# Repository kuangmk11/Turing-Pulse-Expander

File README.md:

# Turing Pulse Expander — archive

> **This repository is an archive.** The finished work has moved out into its own
> repositories; what remains here is upstream material and the studies that were
> superseded along the way.

| Live work | |
|---|---|
| **[Doubleplus_Pulses](https://github.com/kuangmk11/Doubleplus_Pulses)** | **Pulses Plus** — the built and tested hardware. KiCad schematic, PCB, panel v4, BOM, gerbers, and the full design write-up. CC BY-NC-SA 4.0. |
| **[Doubleplus_Pulses_VCV](https://github.com/kuangmk11/Doubleplus_Pulses_VCV)** | The VCV Rack 2 port of the same module. GPL-3.0-or-later. |

Both were extracted with `git subtree split`, so their commit history came with
them. Their files remain in this repository's history too, up to the commit that
removed them — nothing was rewritten here.

---

## What Pulses Plus is

A performance-oriented gate router for the Music Thing Turing Machine: eight pulse
channels, each switchable to one of two merge buses or off, with each bus computing
the OR or the AND of whatever is routed to it, chosen live from the panel. It
generalises the stock Pulses expander's four hard-wired AND outputs into any subset
of the eight bits, OR'd or AND'd, by hand.

See [Doubleplus_Pulses](https://github.com/kuangmk11/Doubleplus_Pulses) for the
design and the write-up.

---

## What's left here

### Upstream: Rev 2 Turing Pulse Expander

This repository is a fork of
[TomWhitwell/Turing-Pulse-Expander](https://github.com/TomWhitwell/Turing-Pulse-Expander),
and keeps that link deliberately — it is the right home for Tom Whitwell's files.

- `Hardware/pulses_rev2.brd`, `Hardware/pulses_rev2.sch` — the original Eagle design
- `Collateral/` — his gerbers, panel artwork and schematic PDF

The Rev 2 expander is a slightly updated Turing Machine Pulse Expander with more
outputs — SMD, but still an easy build. Its BOM:

- 1 × 4081 Quad AND Gate, SO14 package
- 11 × 3 mm LEDs
- 11 × 1k resistors, 1206
- 11 × 2k resistors, 1206 (LED protection — change the value for high-intensity LEDs)
- 11 × [Thonkiconn](https://www.thonk.co.uk/shop/thonkiconn-3-5mm-jack-sockets-x50/) sockets
- 1 × 16-pin header 2×8 (e.g. Mouser 649-67997-216HLF)
- 1 × ribbon cable

### Dead ends and studies

- `Docs/build_*.py`, `kfp.py`, `ksym.py`, `panel_geom.py`, `patch_footprints.py` —
  the generator scripts that built the earlier `pulses_plus` board from source.
  The finished module took a different route: it carries a single, much smaller
  `tools/build_panel.py` that regenerates only panel artwork from the v1 panel.
- `Docs/panel/` — two early panel layout studies (`v1-two-column-grid.html`,
  `v2-zigzag.html`) and the notes comparing them. The zig-zag won and became the
  shipped panel.
- `Hardware/pulses_plus/` — the superseded full-size design that preceded the
  sub-miniature-toggle version. **Present on disk but never committed**; it is
  gitignored and always has been, so it does not exist in this repository's
  history and will not appear in a fresh clone.
- Assorted scratch material at the repository root (`Chat.txt`, `path30.svg`,
  panel artwork exports) — likewise gitignored, on disk only.

---

## Licence

**Tom Whitwell's Rev 2 expander** — `Hardware/pulses_rev2.brd`, `Hardware/pulses_rev2.sch`
and `Collateral/` — is his, inherited by forking
[TomWhitwell/Turing-Pulse-Expander](https://github.com/TomWhitwell/Turing-Pulse-Expander).
Nothing here grants rights over it. For context, the parent
[Turing Machine](https://github.com/TomWhitwell/TuringMachine) project's README states
[CC-BY-SA 3.0](https://creativecommons.org/licenses/by-sa/3.0/), but that is not
stated in the expander repository itself.

**The Pulses Plus studies** in `Docs/` are Missing Mile Modular's, under
[CC BY-NC-SA 4.0](https://creativecommons.org/licenses/by-nc-sa/4.0/) — the same
terms as the finished hardware.

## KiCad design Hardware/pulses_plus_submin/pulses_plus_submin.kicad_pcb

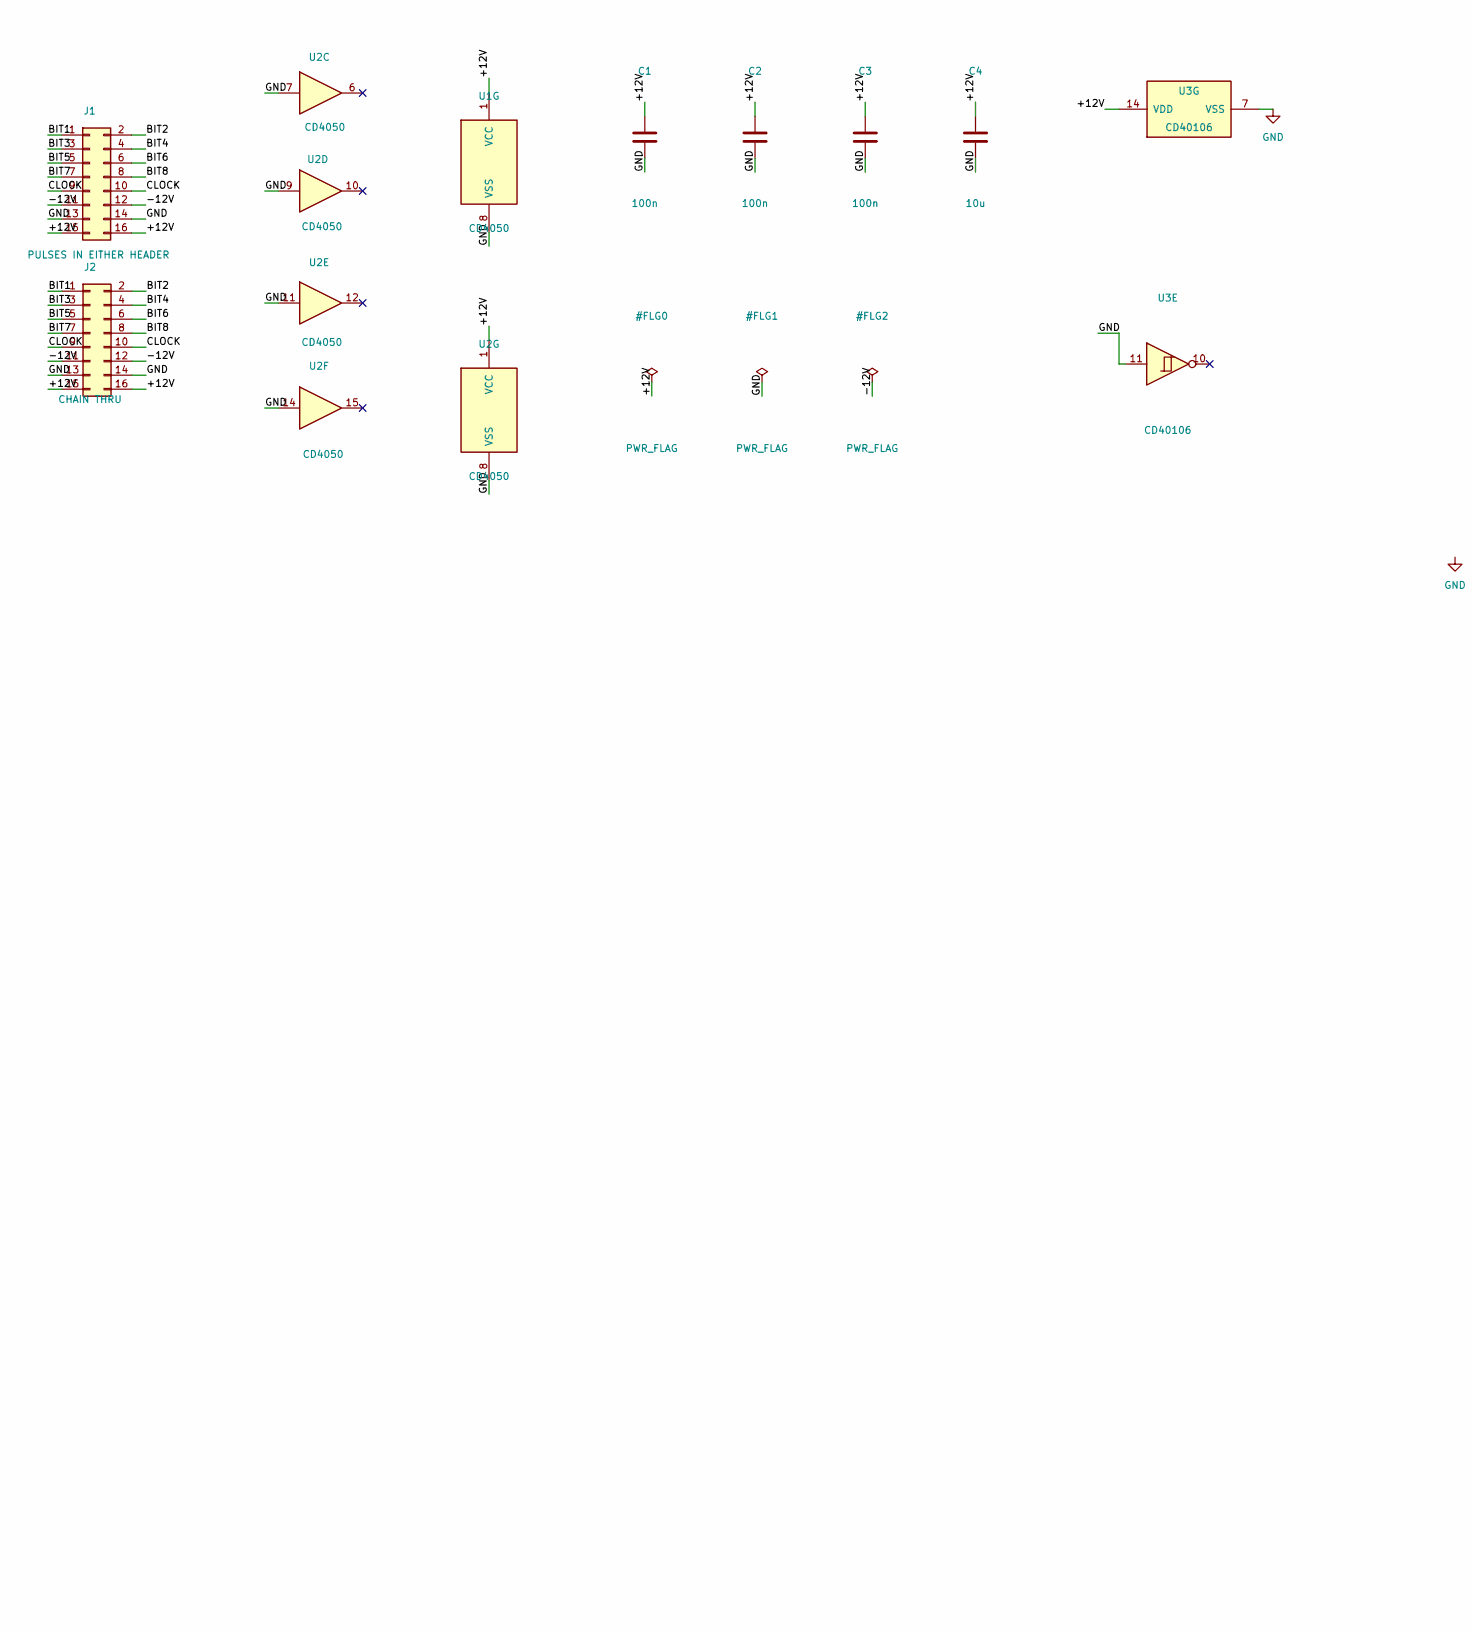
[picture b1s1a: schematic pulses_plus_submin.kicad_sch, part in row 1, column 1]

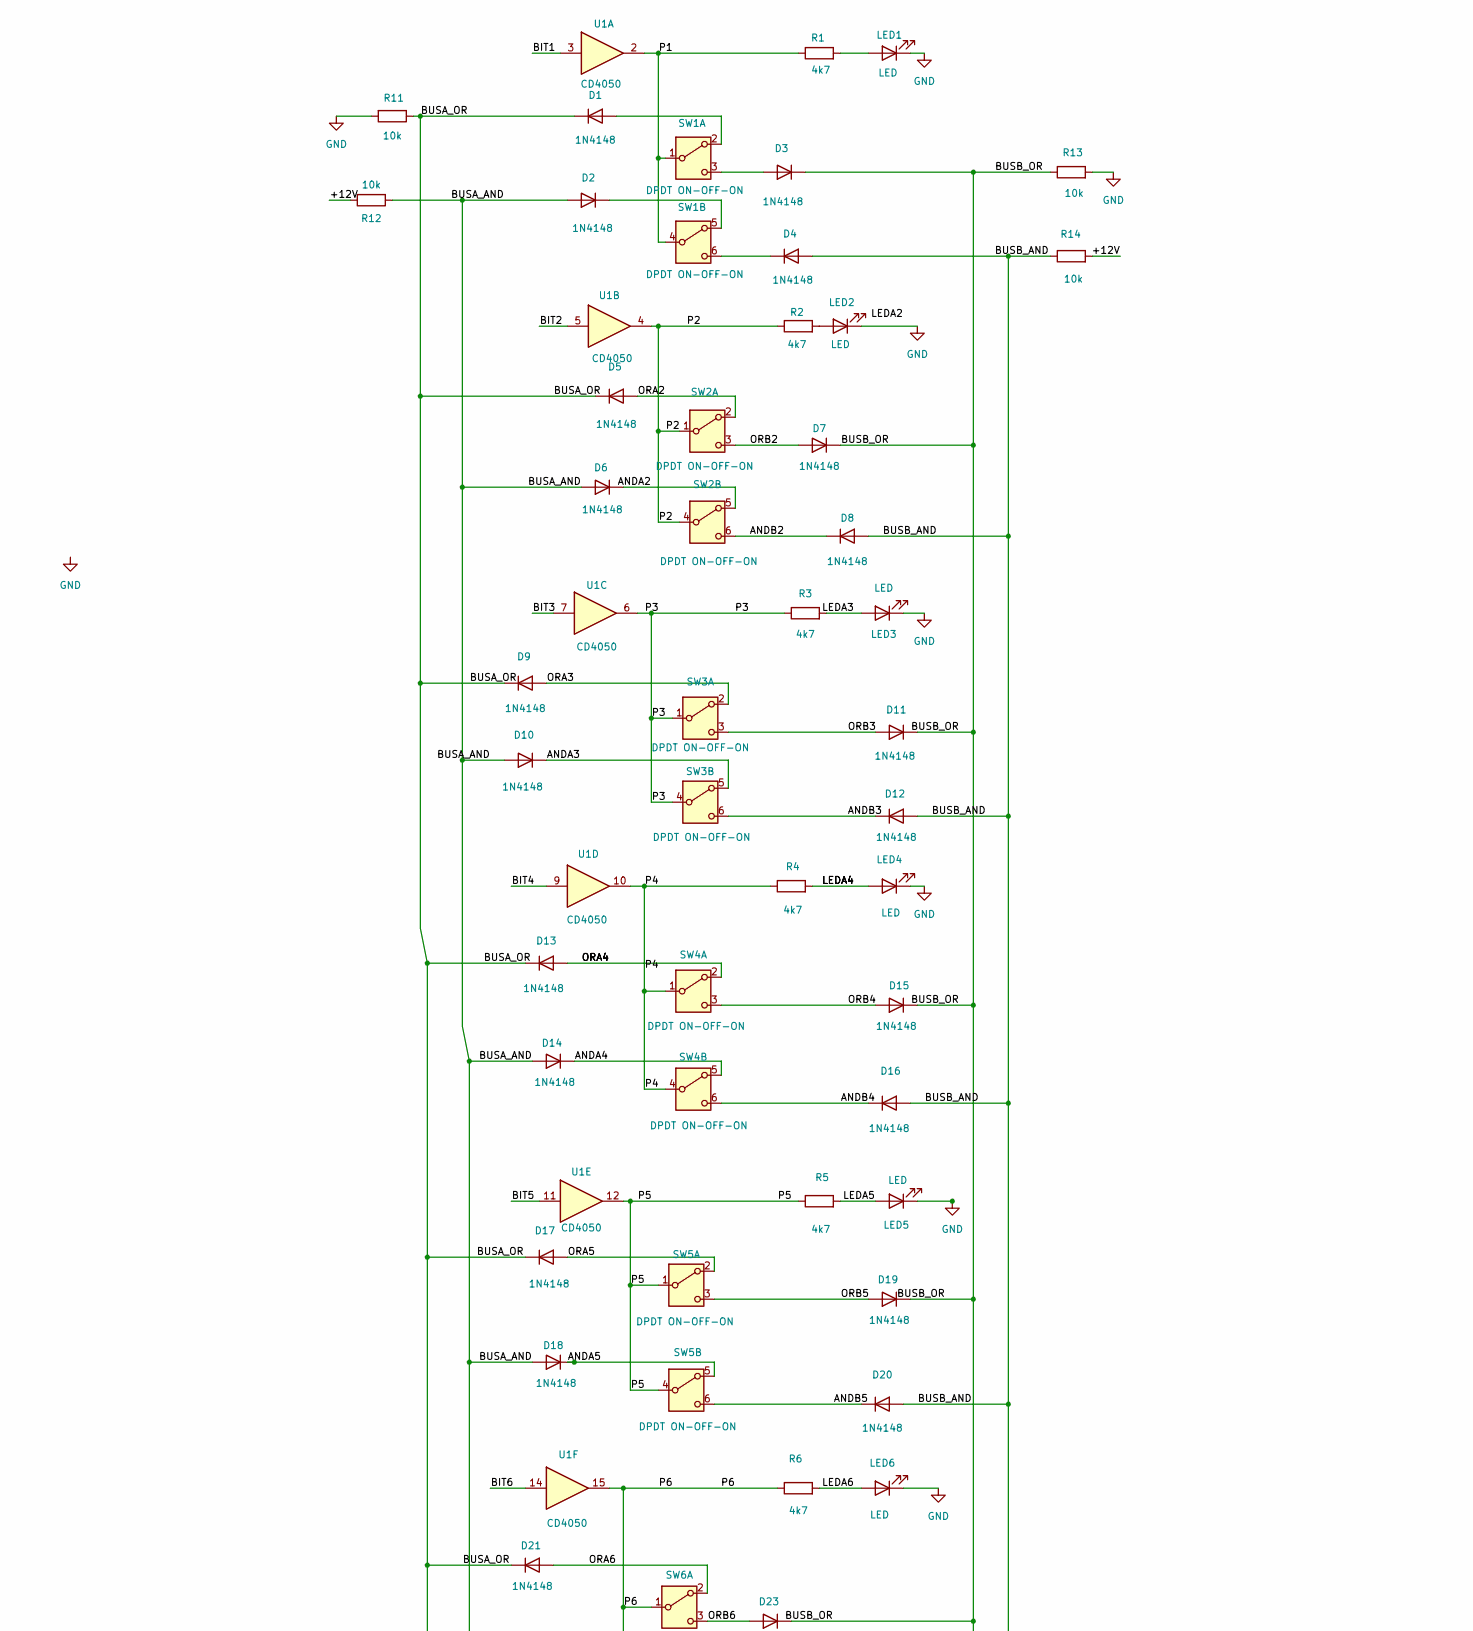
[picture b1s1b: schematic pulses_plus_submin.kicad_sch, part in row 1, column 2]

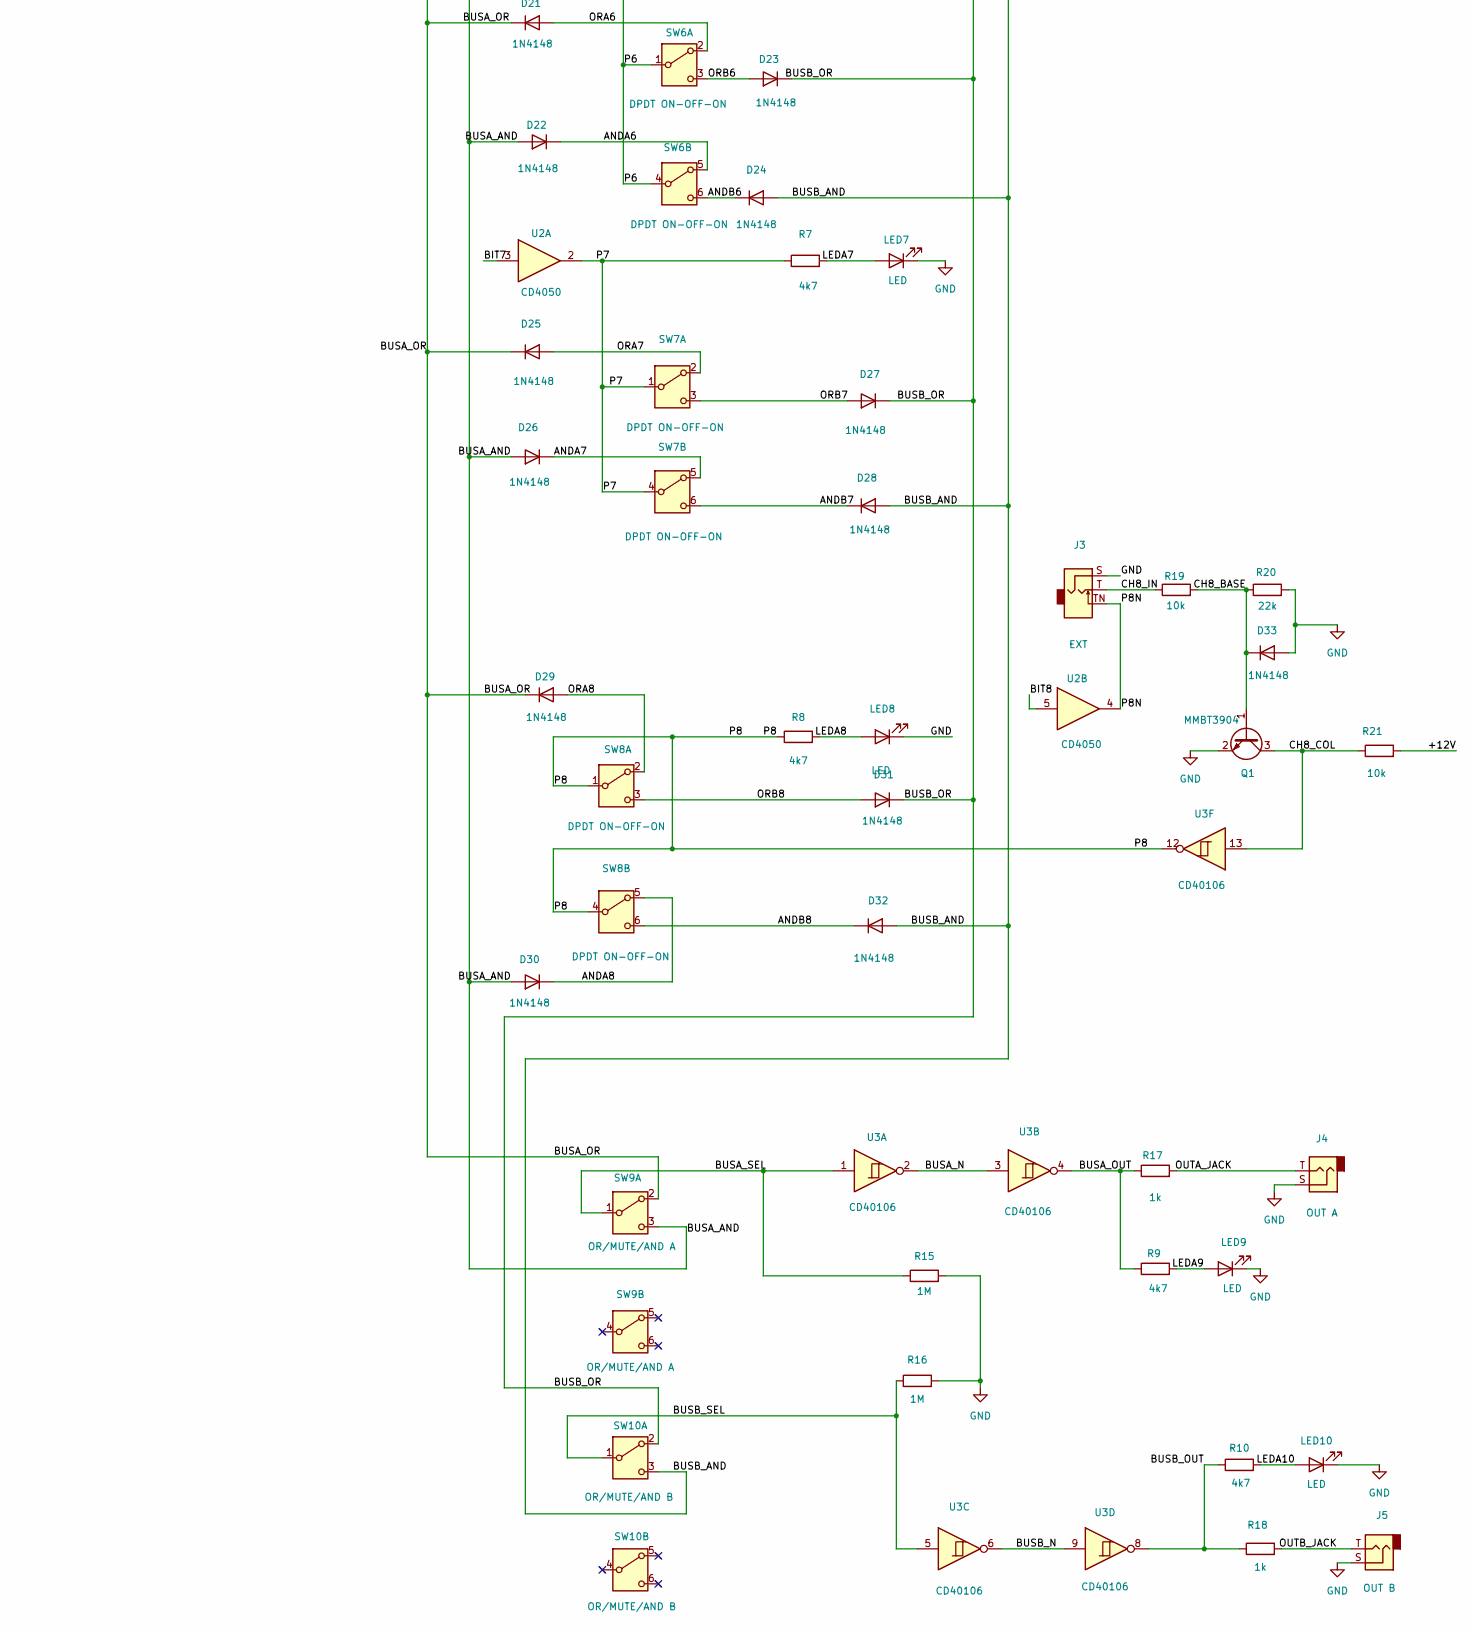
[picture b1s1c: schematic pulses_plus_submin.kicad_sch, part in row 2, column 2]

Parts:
C1, C2, C3: 100n; C_1206_3216Metric_Pad1.33x1.80mm_HandSolder
C4: 10u; C_1206_3216Metric_Pad1.33x1.80mm_HandSolder
D1, D2, D3, D4, D5, D6, D7, D8, D9, D10, D11, D12, D13, D14, D15, D16, D17, D18, D19, D20, D21, D22, D23, D24, D25, D26, D27, D28, D29, D30, D31, D32, D33: 1N4148; D_SOD-123
J1: PULSES IN EITHER HEADER; IDC-Header_2x08_P2.54mm_Vertical
J2: CHAIN THRU; IDC-Header_2x08_P2.54mm_Vertical
J3: EXT; Thonkiconn_PJ301M
J4: OUT A; Thonkiconn_PJ301M
J5: OUT B; Thonkiconn_PJ301M
LED1, LED2, LED3, LED4, LED5, LED6, LED7, LED8, LED9, LED10: LED; LED_D3.0mm
Q1: MMBT3904; SOT-23
R1, R2, R3, R4, R5, R6, R7, R8, R9, R10: 4k7; R_1206_3216Metric_Pad1.30x1.75mm_HandSolder
R11, R12, R13, R14, R19, R21: 10k; R_1206_3216Metric_Pad1.30x1.75mm_HandSolder
R15, R16: 1M; R_1206_3216Metric_Pad1.30x1.75mm_HandSolder
R17, R18: 1k; R_1206_3216Metric_Pad1.30x1.75mm_HandSolder
R20: 22k; R_1206_3216Metric_Pad1.30x1.75mm_HandSolder
SW1, SW2, SW3, SW4, SW5, SW6, SW7, SW8: DPDT ON-OFF-ON; SW_200_MDP3_DPDT
SW9: OR/MUTE/AND A; SW_200_MDP3_DPDT
SW10: OR/MUTE/AND B; SW_200_MDP3_DPDT
U1, U2: CD4050; DIP-16_W7.62mm
U3: CD40106; DIP-14_W7.62mm

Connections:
/+12V: C1.1, C2.1, C3.1, C4.1, J1.15, J1.16, J2.15, J2.16, R12.2, R14.2, R21.2, U1.1 (VCC), U2.1 (VCC), U3.14 (VDD)
/-12V: J1.11, J1.12, J2.11, J2.12
/ANDA2: D6.1 (K), SW2.5 (B)
/ANDA3: D10.1 (K), SW3.5 (B)
/ANDA4: D14.1 (K), SW4.5 (B)
/ANDA5: D18.1 (K), SW5.5 (B)
/ANDA6: D22.1 (K), SW6.5 (B)
/ANDA7: D26.1 (K), SW7.5 (B)
/ANDA8: D30.1 (K), SW8.5 (B)
/ANDB2: D8.1 (K), SW2.6 (C)
/ANDB3: D12.1 (K), SW3.6 (C)
/ANDB4: D16.1 (K), SW4.6 (C)
/ANDB5: D20.1 (K), SW5.6 (C)
/ANDB6: D24.1 (K), SW6.6 (C)
/ANDB7: D28.1 (K), SW7.6 (C)
/ANDB8: D32.1 (K), SW8.6 (C)
/BIT1: J1.1, J2.1, U1.3
/BIT2: J1.2, J2.2, U1.5
/BIT3: J1.3, J2.3, U1.7
/BIT4: J1.4, J2.4, U1.9
/BIT5: J1.5, J2.5, U1.11
/BIT6: J1.6, J2.6, U1.14
/BIT7: J1.7, J2.7, U2.3
/BIT8: J1.8, J2.8, U2.5
/BUSA_AND: D2.2 (A), D6.2 (A), D10.2 (A), D14.2 (A), D18.2 (A), D22.2 (A), D26.2 (A), D30.2 (A), R12.1, SW9.3 (C)
/BUSA_N: U3.2, U3.3
/BUSA_OR: D1.1 (K), D5.1 (K), D9.1 (K), D13.1 (K), D17.1 (K), D21.1 (K), D25.1 (K), D29.1 (K), R11.1, SW9.2 (B)
/BUSA_OUT: R9.1, R17.1, U3.4
/BUSA_SEL: R15.1, SW9.1 (A), U3.1
/BUSB_AND: D4.2 (A), D8.2 (A), D12.2 (A), D16.2 (A), D20.2 (A), D24.2 (A), D28.2 (A), D32.2 (A), R14.1, SW10.3 (C)
/BUSB_N: U3.6, U3.9
/BUSB_OR: D3.1 (K), D7.1 (K), D11.1 (K), D15.1 (K), D19.1 (K), D23.1 (K), D27.1 (K), D31.1 (K), R13.1, SW10.2 (B)
/BUSB_OUT: R10.1, R18.1, U3.8
/BUSB_SEL: R16.1, SW10.1 (A), U3.5
/CH8_BASE: D33.1 (K), Q1.1 (B), R19.2, R20.1
/CH8_COL: Q1.3 (C), R21.1, U3.13
/CH8_IN: J3.T, R19.1
/CLOCK: J1.9, J1.10, J2.9, J2.10
/LEDA3: LED3.2 (A), R3.2
/LEDA5: LED5.2 (A), R5.2
/LEDA6: LED6.2 (A), R6.2
/LEDA7: LED7.2 (A), R7.2
/LEDA8: LED8.2 (A), R8.2
/LEDA9: LED9.2 (A), R9.2
/LEDA10: LED10.2 (A), R10.2
/ORA2: D5.2 (A), SW2.2 (B)
/ORA3: D9.2 (A), SW3.2 (B)
/ORA5: D17.2 (A), SW5.2 (B)
/ORA6: D21.2 (A), SW6.2 (B)
/ORA7: D25.2 (A), SW7.2 (B)
/ORA8: D29.2 (A), SW8.2 (B)
/ORB2: D7.2 (A), SW2.3 (C)
/ORB3: D11.2 (A), SW3.3 (C)
/ORB4: D15.2 (A), SW4.3 (C)
/ORB5: D19.2 (A), SW5.3 (C)
/ORB6: D23.2 (A), SW6.3 (C)
/ORB7: D27.2 (A), SW7.3 (C)
/ORB8: D31.2 (A), SW8.3 (C)
/OUTA_JACK: J4.T, R17.2
/OUTB_JACK: J5.T, R18.2
/P1: R1.1, SW1.1 (A), SW1.4 (A), U1.2
/P2: R2.1, SW2.1 (A), SW2.4 (A), U1.4
/P3: R3.1, SW3.1 (A), SW3.4 (A), U1.6
/P4: R4.1, SW4.1 (A), SW4.4 (A), U1.10
/P5: R5.1, SW5.1 (A), SW5.4 (A), U1.12
/P6: R6.1, SW6.1 (A), SW6.4 (A), U1.15
/P7: R7.1, SW7.1 (A), SW7.4 (A), U2.2
/P8: R8.1, SW8.1 (A), SW8.4 (A), U3.12
/P8N: J3.TN, U2.4
GND: C1.2, C2.2, C3.2, C4.2, D33.2 (A), J1.13, J1.14, J2.13, J2.14, J3.S, J4.S, J5.S, LED1.1 (K), LED2.1 (K), LED3.1 (K), LED4.1 (K), LED5.1 (K), LED6.1 (K), LED7.1 (K), LED8.1 (K), LED9.1 (K), LED10.1 (K), Q1.2 (E), R11.2, R13.2, R15.2, R16.2, R20.2, U1.8 (VSS), U2.7, U2.8 (VSS), U2.9, U2.11, U2.14, U3.7 (VSS), U3.11
unnamed: D1.2 (A), SW1.2 (B)
unnamed: D2.1 (K), SW1.5 (B)
unnamed: D3.2 (A), SW1.3 (C)
unnamed: D4.1 (K), SW1.6 (C)
unnamed: D13.2 (A), SW4.2 (B)
unnamed: LED1.2 (A), R1.2
unnamed: LED2.2 (A), R2.2
unnamed: LED4.2 (A), R4.2

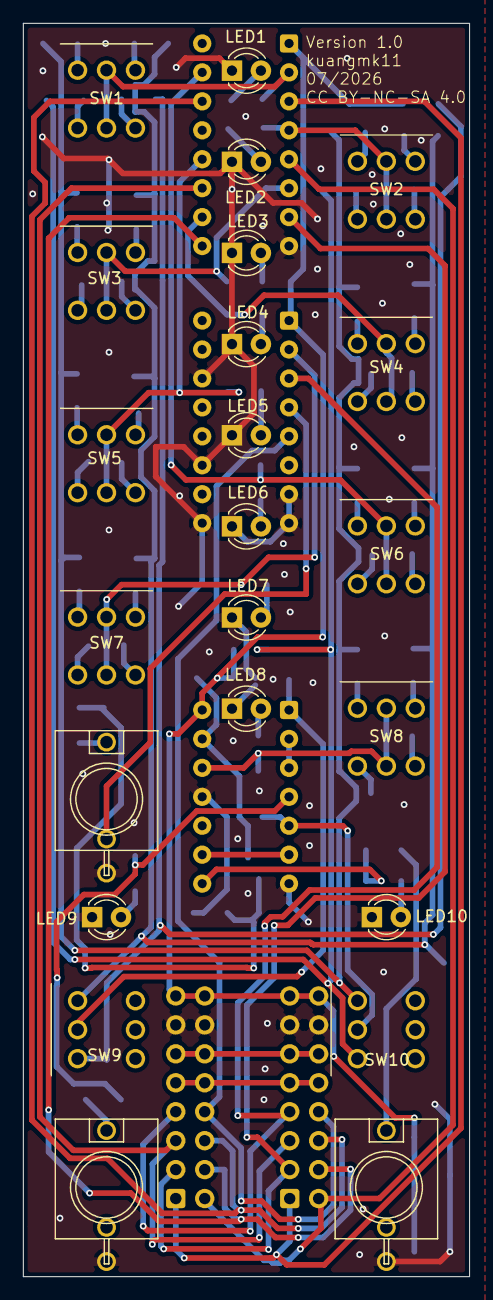
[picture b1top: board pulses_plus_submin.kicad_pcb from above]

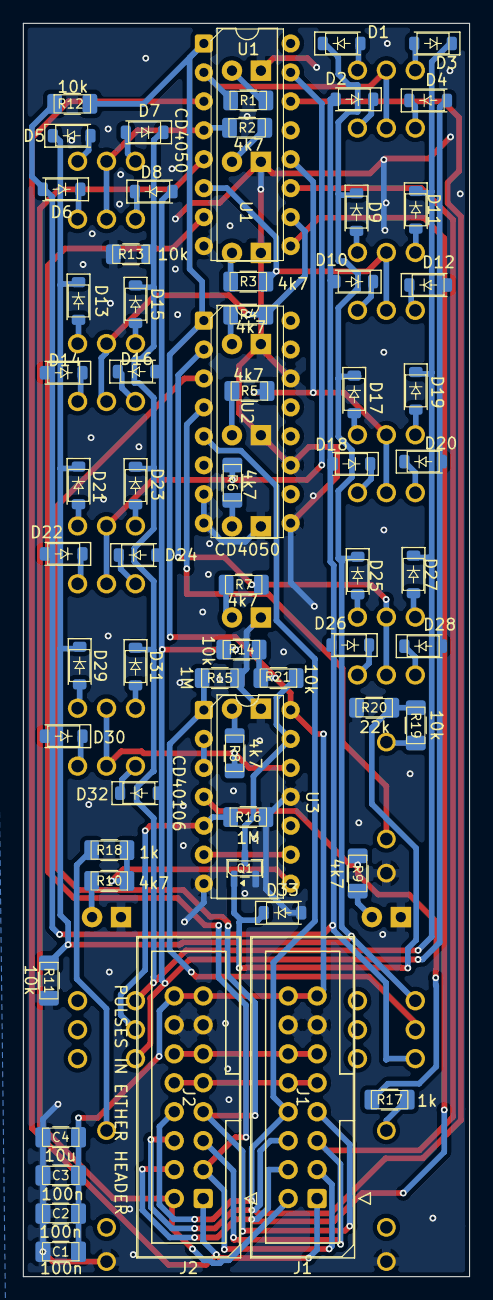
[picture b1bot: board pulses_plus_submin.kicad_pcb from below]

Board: 2 copper layers, 39.2 x 110.0 mm, 87 parts (64 on the bottom side), 78 nets.

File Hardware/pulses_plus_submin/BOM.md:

# Pulses Plus (sub-mini) — Bill of Materials

Generated from `pulses_plus_submin.kicad_sch` (87 placed components, 18 line items).
Two sourcing columns:

- **DigiKey** — for hand assembly (the THT parts and jacks are hand-solder anyway).
- **JLCPCB / LCSC** — the LCSC `C`-number is what JLCPCB SMT assembly needs for the SMD parts.

Switches are sourced from **Love My Switches** (they are the Taiway 200 sub-mini toggles,
not a DigiKey/LCSC stock part).

> ⚠ **Verify before ordering** — part numbers marked *(verify)* are the correct manufacturer
> series but the exact distributor SKU / LCSC stock C-number should be confirmed against live
> stock at order time. Confirmed numbers came from distributor listings and are noted as such.

---

## BOM table

| # | Qty | Value | Refs | Package / Footprint | Mfr Part | DigiKey | JLCPCB / LCSC |
|---|-----|-------|------|---------------------|----------|---------|---------------|
| 1 | 10 | **DPDT ON-OFF-ON toggle** | SW1–SW10 | Taiway 200 sub-mini, PC vertical, ø4.95 bushing | Taiway **200-MDP3-T2B1M2QE** | — | — |
| 2 | 2 | CD4050 hex buffer | U1, U2 | DIP-16 | **CD4050BE** (TI) | 296-2056-ND | C(verify) |
| 3 | 1 | CD40106 hex Schmitt | U3 | DIP-14 | **CD40106BE** (TI) | 296-9797-5-ND *(verify)* | **C71251** |
| 4 | 1 | MMBT3904 NPN | Q1 | SOT-23 | **MMBT3904** | MMBT3904FSCT-ND | **C20526** |
| 5 | 33 | 1N4148 switching diode | D1–D33 | SOD-123 (`Diode_SMD:D_SOD-123`) | **1N4148W** | 1N4148W-FDICT-ND | **C81598** |
| 6 | 10 | 4k7 resistor | R1–R10 | 1206, 1% | Yageo **RC1206FR-074K7L** | search mfr PN | C(verify) |
| 7 | 6 | 10k resistor | R11–R14, R19, R21 | 1206, 1% | Yageo **RC1206FR-0710KL** | search mfr PN | C(verify) |
| 8 | 2 | 1k resistor | R17, R18 | 1206, 1% | Yageo **RC1206FR-071KL** | search mfr PN | C(verify) |
| 9 | 1 | 22k resistor | R20 | 1206, 1% | Yageo **RC1206FR-0722KL** | search mfr PN | C(verify) |
| 10 | 2 | 1M resistor | R15, R16 | 1206, 1% | Yageo **RC1206FR-071ML** | search mfr PN | C(verify) |
| 11 | 3 | 100n capacitor | C1, C2, C3 | 1206, X7R, 50V | Samsung **CL31B104KBCNNNC** | 1276-1092-1-ND *(verify)* | C(verify) |
| 12 | 1 | 10µ capacitor | C4 | 1206, X5R, 25V | Samsung **CL31A106KBHNNNE** | 1276-1940-1-ND *(verify)* | C(verify) |
| 13 | 10 | 3mm LED, high-brightness | LED1–LED10 | 3mm THT | e.g. Kingbright WP710A10 series | any 3mm LED | — |
| 14 | 3 | 3.5mm mono jack "Thonkiconn" | J3 (EXT, switched), J4 (OUT A), J5 (OUT B) | PJ301M-12 / PJ398SM | **PJ398SM** | not stocked | not stocked |
| 15 | 2 | 2×8 IDC box header, 2.54mm | J1 (PULSES IN), J2 (CHAIN THRU) | shrouded, vertical | generic 2x8 IDC | 2×8 shrouded header | C(verify) |

**J3 must be the switched (normalling) variant** — its break contact normals buffered BIT8 into
channel 8. J4/J5 are plain mono. All three are the same Thonkiconn body.

---

## Sourcing notes

**Switches (SW1–SW10) — Love My Switches**
Taiway **200-MDP3-T2B1M2QE**, "Sub-Mini DPDT On-Off-On, PCB Mount, Short Shaft."
~$2.15 ea (≈ $21.50 for 10). Body 8.1 × 23.2 mm, ships with two nuts + a washer.
Product page: <https://lovemyswitches.com/taiway-sub-mini-dpdt-on-off-on-sw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
Panel hole is ø4.95 mm (10-48 UNS bushing). All 10 switches are this one part.

**Thonkiconn jacks (J3/J4/J5)** — not a DigiKey/LCSC catalog part. Buy from Thonk, Love My
Switches, Synthrotek, or Oddvolt (PJ398SM / PJ301M-12; the two are interchangeable). If you want
JLCPCB to place them, you'll need to supply them as a consigned part or substitute a catalog jack
with the same footprint.

**Resistors** — Yageo RC1206 series part numbers above are deterministic (`RC1206FR-07` + value
code + `L`, F = 1%). Any 1206 thick-film at 1% is fine; values are non-critical. On JLCPCB these
are Basic parts — pick the in-stock C-number for each value in the parts tool.

**Ceramics** — 100n/10µ 1206 X7R/X5R; any reputable 1206 MLCC works. The Samsung CL31 series
numbers are representative JLCPCB Basic parts.

---

## Action items before fab

1. **Diode footprint — DONE on the board, still needs the schematic.** All 33 diodes (D1–D33)
   are now on `Diode_SMD:D_SOD-123` on the PCB, part **1N4148W / C81598 / DK 1N4148W-FDICT-ND**.
   Nets verified intact after the swap (8 diodes per bus, pad 1 = K → bus/GND, pad 2 = A).
   > ⚠ **The change was made in the PCB only — the schematic Footprint fields still read
   > `D_1206_3216Metric` (33 of them).** Until those are updated, *Update PCB from Schematic* will
   > revert all 33 diodes to 1206. Fix in KiCad: **pcbnew → Tools → Update Schematic from PCB**
   > (back-annotate footprints), or in the schematic editor set the Footprint field of D1–D33 to
   > `Diode_SMD:D_SOD-123` via **Tools → Edit Symbol Fields**.

2. **Meter the switch** — confirm centre pin = common on the actual Taiway part before committing
   to a board run (design open-question #1). Everything assumes centre-is-common.

3. **LED polarity/brightness** — footprint pad 1 = cathode → GND, pad 2 = anode → 4k7. Use
   modern high-brightness 3mm LEDs (drive is only ~2 mA through 4k7 from a CD4050 output at 12 V).

---

## Verified vs. representative

| Confirmed from distributor listings | Representative (confirm at order) |
|---|---|
| Taiway 200-MDP3-T2B1M2QE (Love My Switches) | CD4050BE LCSC C-number |
| CD4050BE — DigiKey 296-2056-ND | CD40106BE DigiKey SKU |
| CD40106BE — LCSC C71251 | all passive LCSC C-numbers |
| MMBT3904 — LCSC C20526 | ceramic cap DigiKey SKUs |
| 1N4148W — LCSC C81598, DigiKey 1N4148W-FDICT-ND | LED / IDC header specifics |

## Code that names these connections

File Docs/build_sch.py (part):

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    i, o = BUF[u]
    u2_units[u] = (115 + (u - 1) * 30, 85)
    if u == 1:
        u2_pins[i], u2_pins[o] = "BIT7", "P7"
    elif u == 2:
        u2_pins[i], u2_pins[o] = "BIT8", "P8N"
    else:
        u2_pins[i] = "GND"                             # unused CMOS inputs must not float
        u2_pins[o] = None                              # spare output -> no-connect
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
